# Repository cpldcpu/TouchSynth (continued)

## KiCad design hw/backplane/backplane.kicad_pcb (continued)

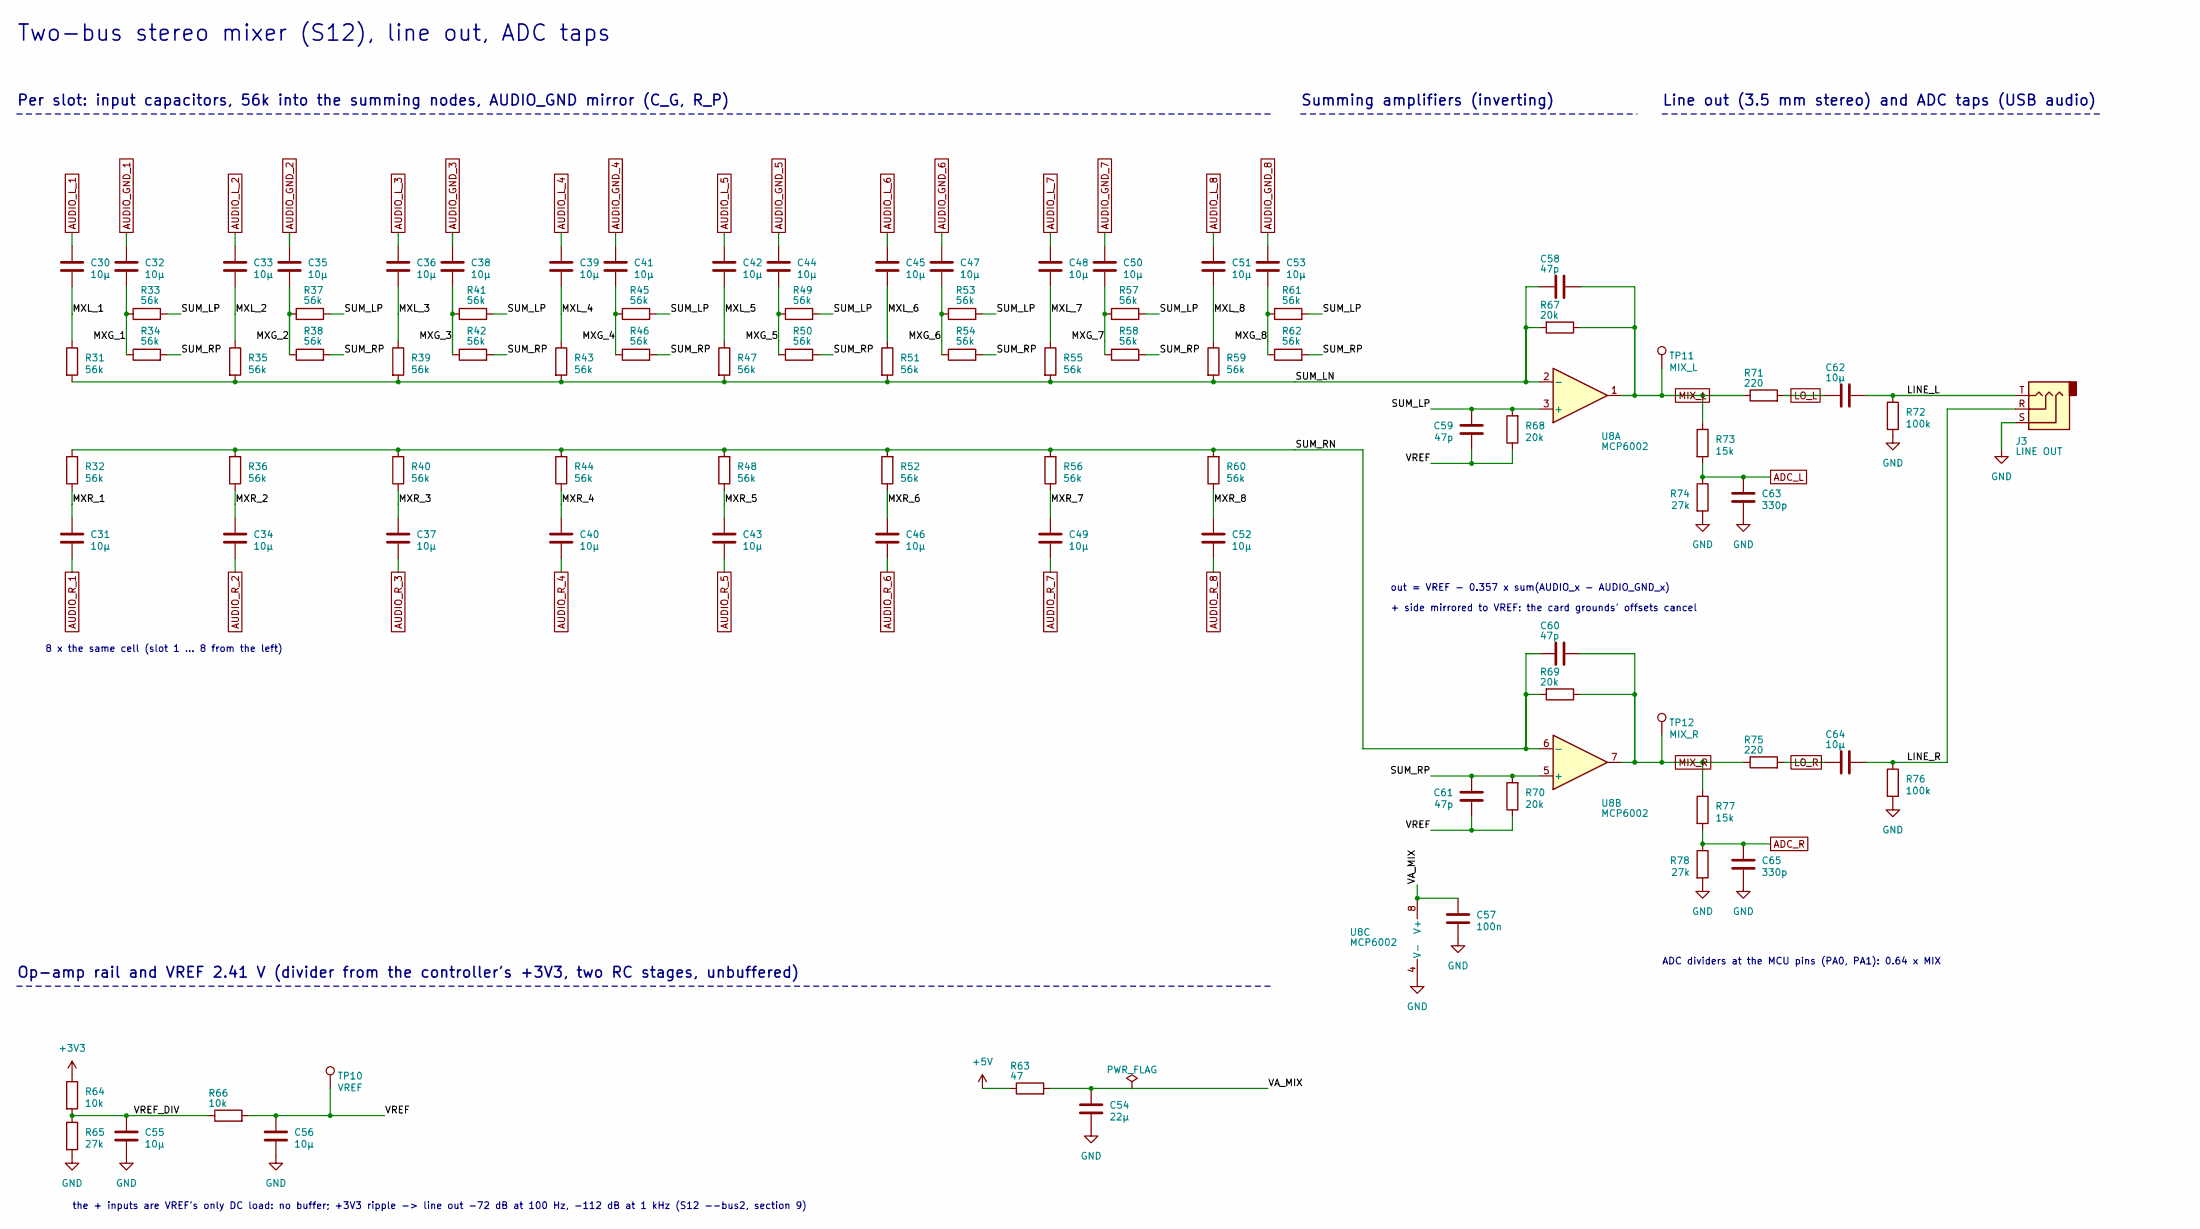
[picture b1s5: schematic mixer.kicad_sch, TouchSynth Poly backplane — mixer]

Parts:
C30, C31, C32, C33, C34, C35, C36, C37, C38, C39, C40, C41, C42, C43, C44, C45, C46, C47, C48, C49, C50, C51, C52, C53: 10µ; C_0805_2012Metric; LCSC C15850
C54: 22µ; C_0805_2012Metric; LCSC C45783
C55, C56, C62, C64: 10µ; C_0603_1608Metric; LCSC C19702
C57: 100n; C_0603_1608Metric; LCSC C14663
C58, C59, C60, C61: 47p; C_0603_1608Metric; LCSC C1671
C63, C65: 330p; C_0603_1608Metric; LCSC C1664
J3: LINE OUT; Jack_3.5mm_CUI_SJ1-3523N_Horizontal
R31, R32, R33, R34, R35, R36, R37, R38, R39, R40, R41, R42, R43, R44, R45, R46, R47, R48, R49, R50, R51, R52, R53, R54, R55, R56, R57, R58, R59, R60, R61, R62: 56k; R_0603_1608Metric; LCSC C23206
R63: 47; R_0603_1608Metric; LCSC C23182
R64, R66: 10k; R_0603_1608Metric; LCSC C25804
R65, R74, R78: 27k; R_0603_1608Metric; LCSC C22967
R67, R68, R69, R70: 20k; R_0603_1608Metric; LCSC C4184
R71, R75: 220; R_0603_1608Metric; LCSC C22962
R72, R76: 100k; R_0603_1608Metric; LCSC C25803
R73, R77: 15k; R_0603_1608Metric; LCSC C22809
TP10: VREF; TestPoint_Pad_D1.0mm
TP11: MIX_L; TestPoint_Pad_D1.0mm
TP12: MIX_R; TestPoint_Pad_D1.0mm
U8: MCP6002; SOIC-8_3.9x4.9mm_P1.27mm; LCSC C7377

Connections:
+3V3: R64.1; also elsewhere on the board
+5V: R63.1; also elsewhere on the board
/mixer/LINE_L: C62.2, J3.T, R72.1
/mixer/LINE_R: C64.2, J3.R, R76.1
/mixer/MXG_1: C32.2, R33.1, R34.1
/mixer/MXG_2: C35.2, R37.1, R38.1
/mixer/MXG_3: C38.2, R41.1, R42.1
/mixer/MXG_4: C41.2, R45.1, R46.1
/mixer/MXG_5: C44.2, R49.1, R50.1
/mixer/MXG_6: C47.2, R53.1, R54.1
/mixer/MXG_7: C50.2, R57.1, R58.1
/mixer/MXG_8: C53.2, R61.1, R62.1
/mixer/MXL_1: C30.2, R31.1
/mixer/MXL_2: C33.2, R35.1
/mixer/MXL_3: C36.2, R39.1
/mixer/MXL_4: C39.2, R43.1
/mixer/MXL_5: C42.2, R47.1
/mixer/MXL_6: C45.2, R51.1
/mixer/MXL_7: C48.2, R55.1
/mixer/MXL_8: C51.2, R59.1
/mixer/MXR_1: C31.2, R32.1
/mixer/MXR_2: C34.2, R36.1
/mixer/MXR_3: C37.2, R40.1
/mixer/MXR_4: C40.2, R44.1
/mixer/MXR_5: C43.2, R48.1
/mixer/MXR_6: C46.2, R52.1
/mixer/MXR_7: C49.2, R56.1
/mixer/MXR_8: C52.2, R60.1
/mixer/SUM_LN: C58.2, R31.2, R35.2, R39.2, R43.2, R47.2, R51.2, R55.2, R59.2, R67.2, U8.2 (-)
/mixer/SUM_LP: C59.2, R33.2, R37.2, R41.2, R45.2, R49.2, R53.2, R57.2, R61.2, R68.2, U8.3 (+)
/mixer/SUM_RN: C60.2, R32.2, R36.2, R40.2, R44.2, R48.2, R52.2, R56.2, R60.2, R69.2, U8.6 (-)
/mixer/SUM_RP: C61.2, R34.2, R38.2, R42.2, R46.2, R50.2, R54.2, R58.2, R62.2, R70.2, U8.5 (+)
/mixer/VA_MIX: C54.1, C57.1, R63.2, U8.8 (V+)
/mixer/VREF: C56.1, C59.1, C61.1, R66.2, R68.1, R70.1, TP10.1
/mixer/VREF_DIV: C55.1, R64.2, R65.1, R66.1
ADC_L: C63.1, R73.2, R74.1; also elsewhere on the board
ADC_R: C65.1, R77.2, R78.1; also elsewhere on the board
AUDIO_GND_1: C32.1; also elsewhere on the board
AUDIO_GND_2: C35.1; also elsewhere on the board
AUDIO_GND_3: C38.1; also elsewhere on the board
AUDIO_GND_4: C41.1; also elsewhere on the board
AUDIO_GND_5: C44.1; also elsewhere on the board
AUDIO_GND_6: C47.1; also elsewhere on the board
AUDIO_GND_7: C50.1; also elsewhere on the board
AUDIO_GND_8: C53.1; also elsewhere on the board
AUDIO_L_1: C30.1; also elsewhere on the board
AUDIO_L_2: C33.1; also elsewhere on the board
AUDIO_L_3: C36.1; also elsewhere on the board
AUDIO_L_4: C39.1; also elsewhere on the board
AUDIO_L_5: C42.1; also elsewhere on the board
AUDIO_L_6: C45.1; also elsewhere on the board
AUDIO_L_7: C48.1; also elsewhere on the board
AUDIO_L_8: C51.1; also elsewhere on the board
AUDIO_R_1: C31.1; also elsewhere on the board
AUDIO_R_2: C34.1; also elsewhere on the board
AUDIO_R_3: C37.1; also elsewhere on the board
AUDIO_R_4: C40.1; also elsewhere on the board
AUDIO_R_5: C43.1; also elsewhere on the board
AUDIO_R_6: C46.1; also elsewhere on the board
AUDIO_R_7: C49.1; also elsewhere on the board
AUDIO_R_8: C52.1; also elsewhere on the board
GND: C54.2, C55.2, C56.2, C57.2, C63.2, C65.2, J3.S, R65.2, R72.2, R74.2, R76.2, R78.2, U8.4 (V-); also elsewhere on the board
LO_L: C62.1, R71.2; also elsewhere on the board
LO_R: C64.1, R75.2; also elsewhere on the board
MIX_L: C58.1, R67.1, R71.1, R73.1, TP11.1, U8.1; also elsewhere on the board
MIX_R: C60.1, R69.1, R75.1, R77.1, TP12.1, U8.7; also elsewhere on the board

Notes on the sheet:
Two-bus stereo mixer (S12), line out, ADC taps
Per slot: input capacitors, 56k into the summing nodes, AUDIO_GND mirror (C_G, R_P)
8 x the same cell (slot 1 ... 8 from the left)
Summing amplifiers (inverting)
out = VREF - 0.357 x sum(AUDIO_x - AUDIO_GND_x)
+ side mirrored to VREF: the card grounds' offsets cancel
Line out (3.5 mm stereo) and ADC taps (USB audio)
ADC dividers at the MCU pins (PA0, PA1): 0.64 x MIX
Op-amp rail and VREF 2.41 V (divider from the controller's +3V3, two RC stages, unbuffered)
the + inputs are VREF's only DC load: no buffer; +3V3 ripple -> line out -72 dB at 100 Hz, -112 dB at 1 kHz (S12 --bus2, section 9)

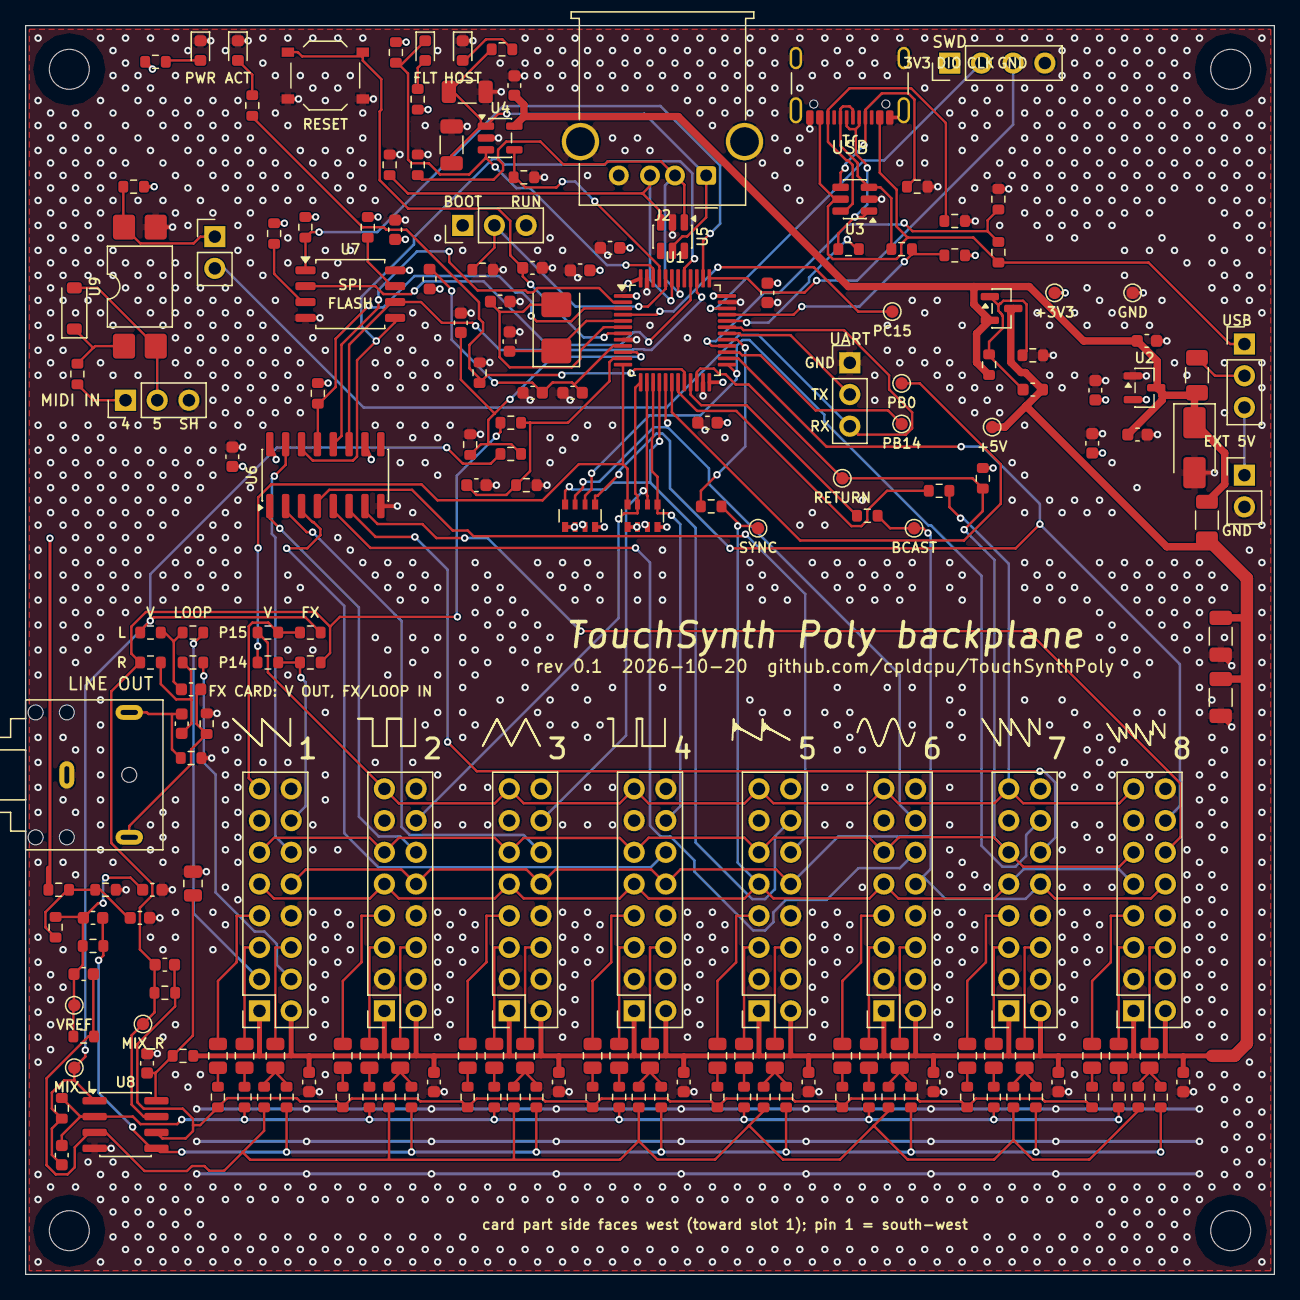
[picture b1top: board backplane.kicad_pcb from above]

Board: 4 copper layers, 100.0 x 100.0 mm, 205 parts (0 on the bottom side), 139 nets.

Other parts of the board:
H1, H2, H3, H4: M3; MountingHole_3.2mm_M3

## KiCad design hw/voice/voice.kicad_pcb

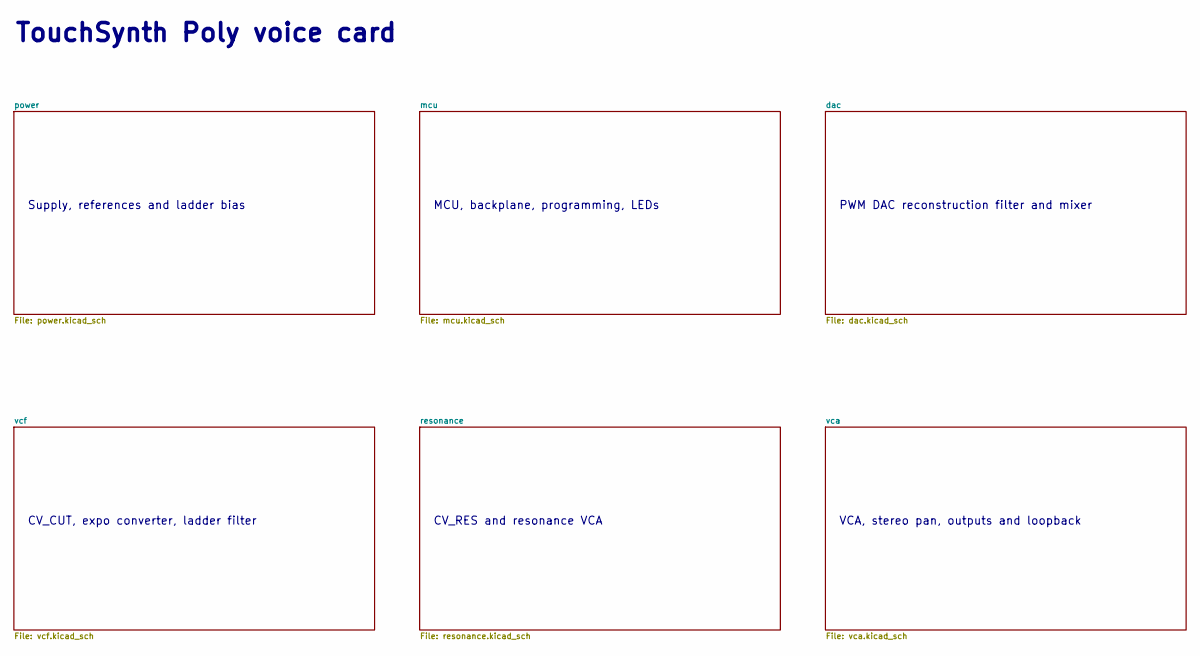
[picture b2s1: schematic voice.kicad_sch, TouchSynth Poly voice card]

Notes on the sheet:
Supply, references and ladder bias
MCU, backplane, programming, LEDs
PWM DAC reconstruction filter and mixer
CV_CUT, expo converter, ladder filter
CV_RES and resonance VCA
VCA, stereo pan, outputs and loopback
TouchSynth Poly voice card

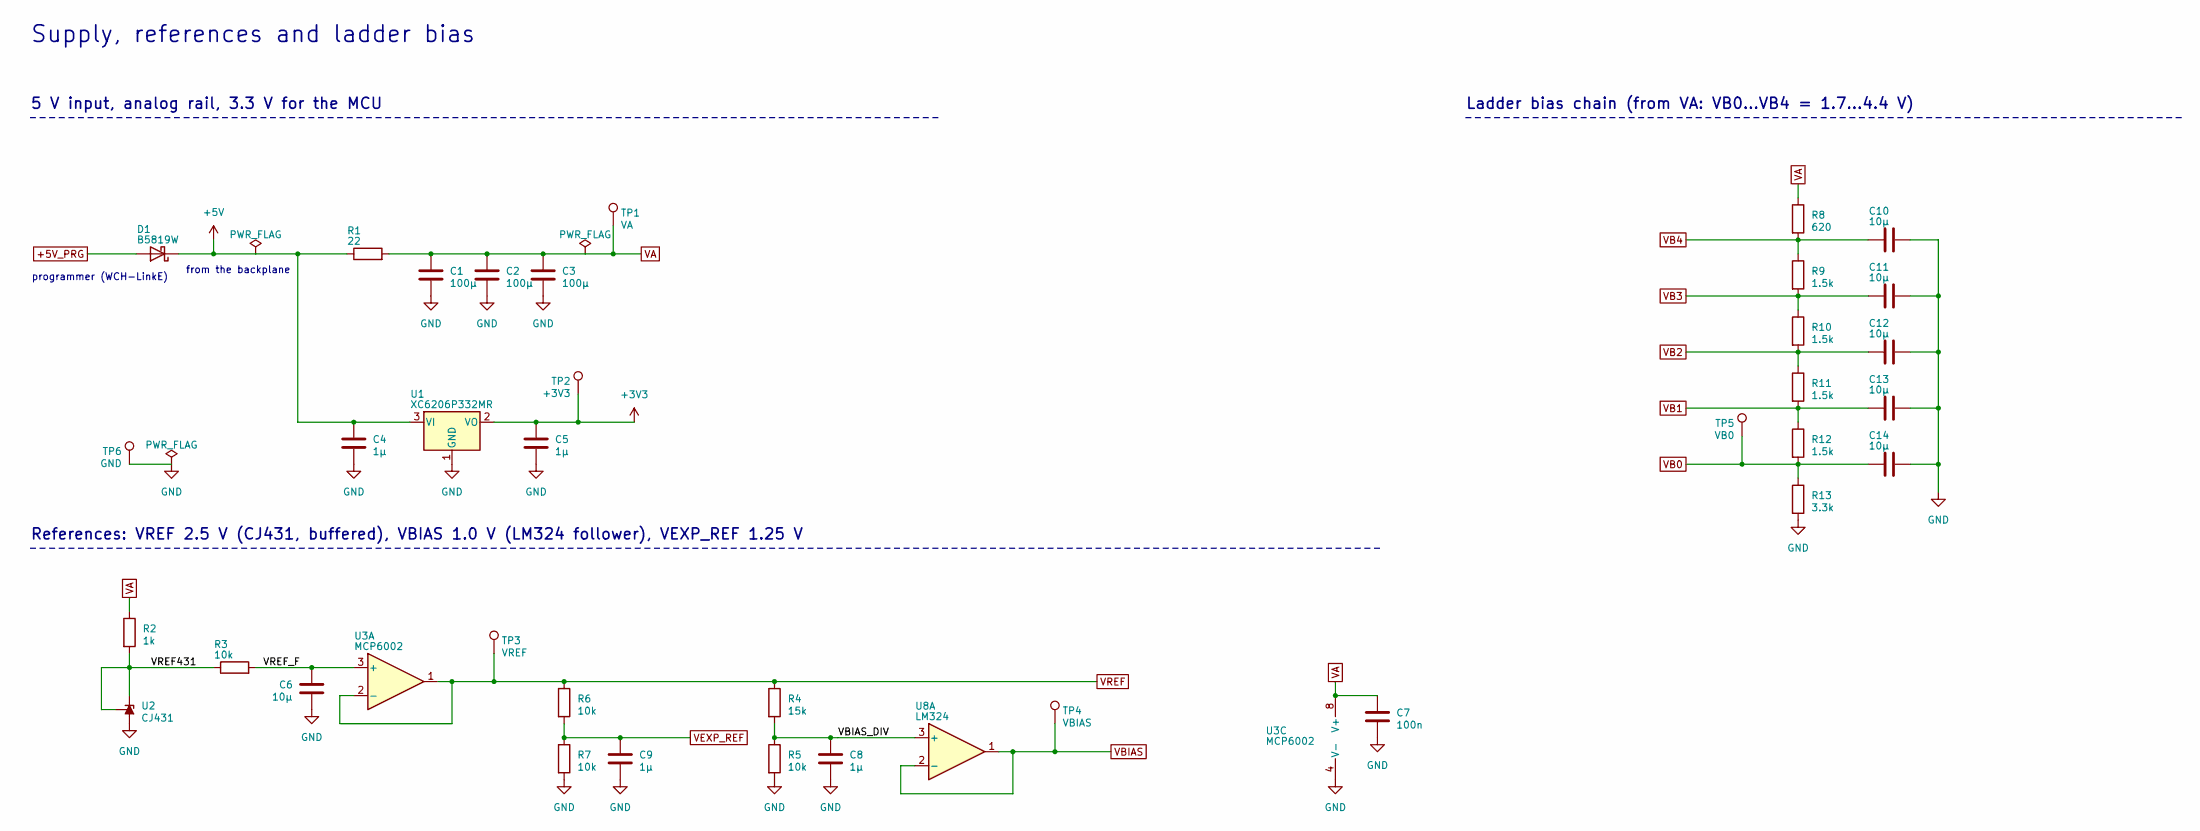
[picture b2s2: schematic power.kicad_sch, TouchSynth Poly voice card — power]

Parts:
C1, C2, C3: 100µ; C_1206_3216Metric; LCSC C15008
C4, C5, C8, C9: 1µ; C_0402_1005Metric; LCSC C52923
C6, C12, C13, C14: 10µ; C_0402_1005Metric; LCSC C15525
C7: 100n; C_0402_1005Metric; LCSC C1525
C10, C11: 10µ; C_0603_1608Metric; LCSC C19702
D1: B5819W; D_SOD-123; LCSC C8598
R1: 22; R_0402_1005Metric; LCSC C25092
R2: 1k; R_0402_1005Metric; LCSC C11702
R3, R5, R6, R7: 10k; R_0402_1005Metric; LCSC C25744
R4: 15k; R_0402_1005Metric; LCSC C25756
R8: 620; R_0603_1608Metric; LCSC C23220
R9, R10, R11, R12: 1.5k; R_0402_1005Metric; LCSC C25867
R13: 3.3k; R_0402_1005Metric; LCSC C25890
TP1: VA; TestPoint_Pad_D1.0mm
TP2: +3V3; TestPoint_Pad_D1.0mm
TP3: VREF; TestPoint_Pad_D1.0mm
TP4: VBIAS; TestPoint_Pad_D1.0mm
TP5: VB0; TestPoint_Pad_D1.0mm
TP6: GND; TestPoint_Pad_D1.0mm
U1: XC6206P332MR; SOT-23; LCSC C5446
U2: CJ431; SOT-23; LCSC C3113
U3: MCP6002; SOIC-8_3.9x4.9mm_P1.27mm; LCSC C7377
U8: LM324; SOIC-14_3.9x8.7mm_P1.27mm; LCSC C71035

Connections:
+3V3: C5.1, TP2.1, U1.2 (VO); also elsewhere on the board
+5V: C4.1, D1.1 (K), R1.1, U1.3 (VI); also elsewhere on the board
+5V_PRG: D1.2 (A); also elsewhere on the board
/power/VBIAS_DIV: C8.1, R4.2, R5.1, U8.3 (+)
/power/VREF431: R2.2, R3.1, U2.1 (REF), U2.2 (K)
/power/VREF_F: C6.1, R3.2, U3.3 (+)
GND: C1.2, C2.2, C3.2, C4.2, C5.2, C6.2, C7.2, C8.2, C9.2, C10.2, C11.2, C12.2, C13.2, C14.2, R5.2, R7.2, R13.2, TP6.1, U1.1 (GND), U2.3 (A), U3.4 (V-); also elsewhere on the board
VA: C1.1, C2.1, C3.1, C7.1, R1.2, R2.1, R8.1, TP1.1, U3.8 (V+); also elsewhere on the board
VB0: C14.1, R12.2, R13.1, TP5.1; also elsewhere on the board
VB1: C13.1, R11.2, R12.1; also elsewhere on the board
VB2: C12.1, R10.2, R11.1; also elsewhere on the board
VB3: C11.1, R9.2, R10.1; also elsewhere on the board
VB4: C10.1, R8.2, R9.1; also elsewhere on the board
VBIAS: TP4.1, U8.1, U8.2 (-); also elsewhere on the board
VEXP_REF: C9.1, R6.2, R7.1; also elsewhere on the board
VREF: R4.1, R6.1, TP3.1, U3.1, U3.2 (-); also elsewhere on the board

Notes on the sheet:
Supply, references and ladder bias
5 V input, analog rail, 3.3 V for the MCU
programmer (WCH-LinkE)
from the backplane
References: VREF 2.5 V (CJ431, buffered), VBIAS 1.0 V (LM324 follower), VEXP_REF 1.25 V
Ladder bias chain (from VA: VB0...VB4 = 1.7...4.4 V)

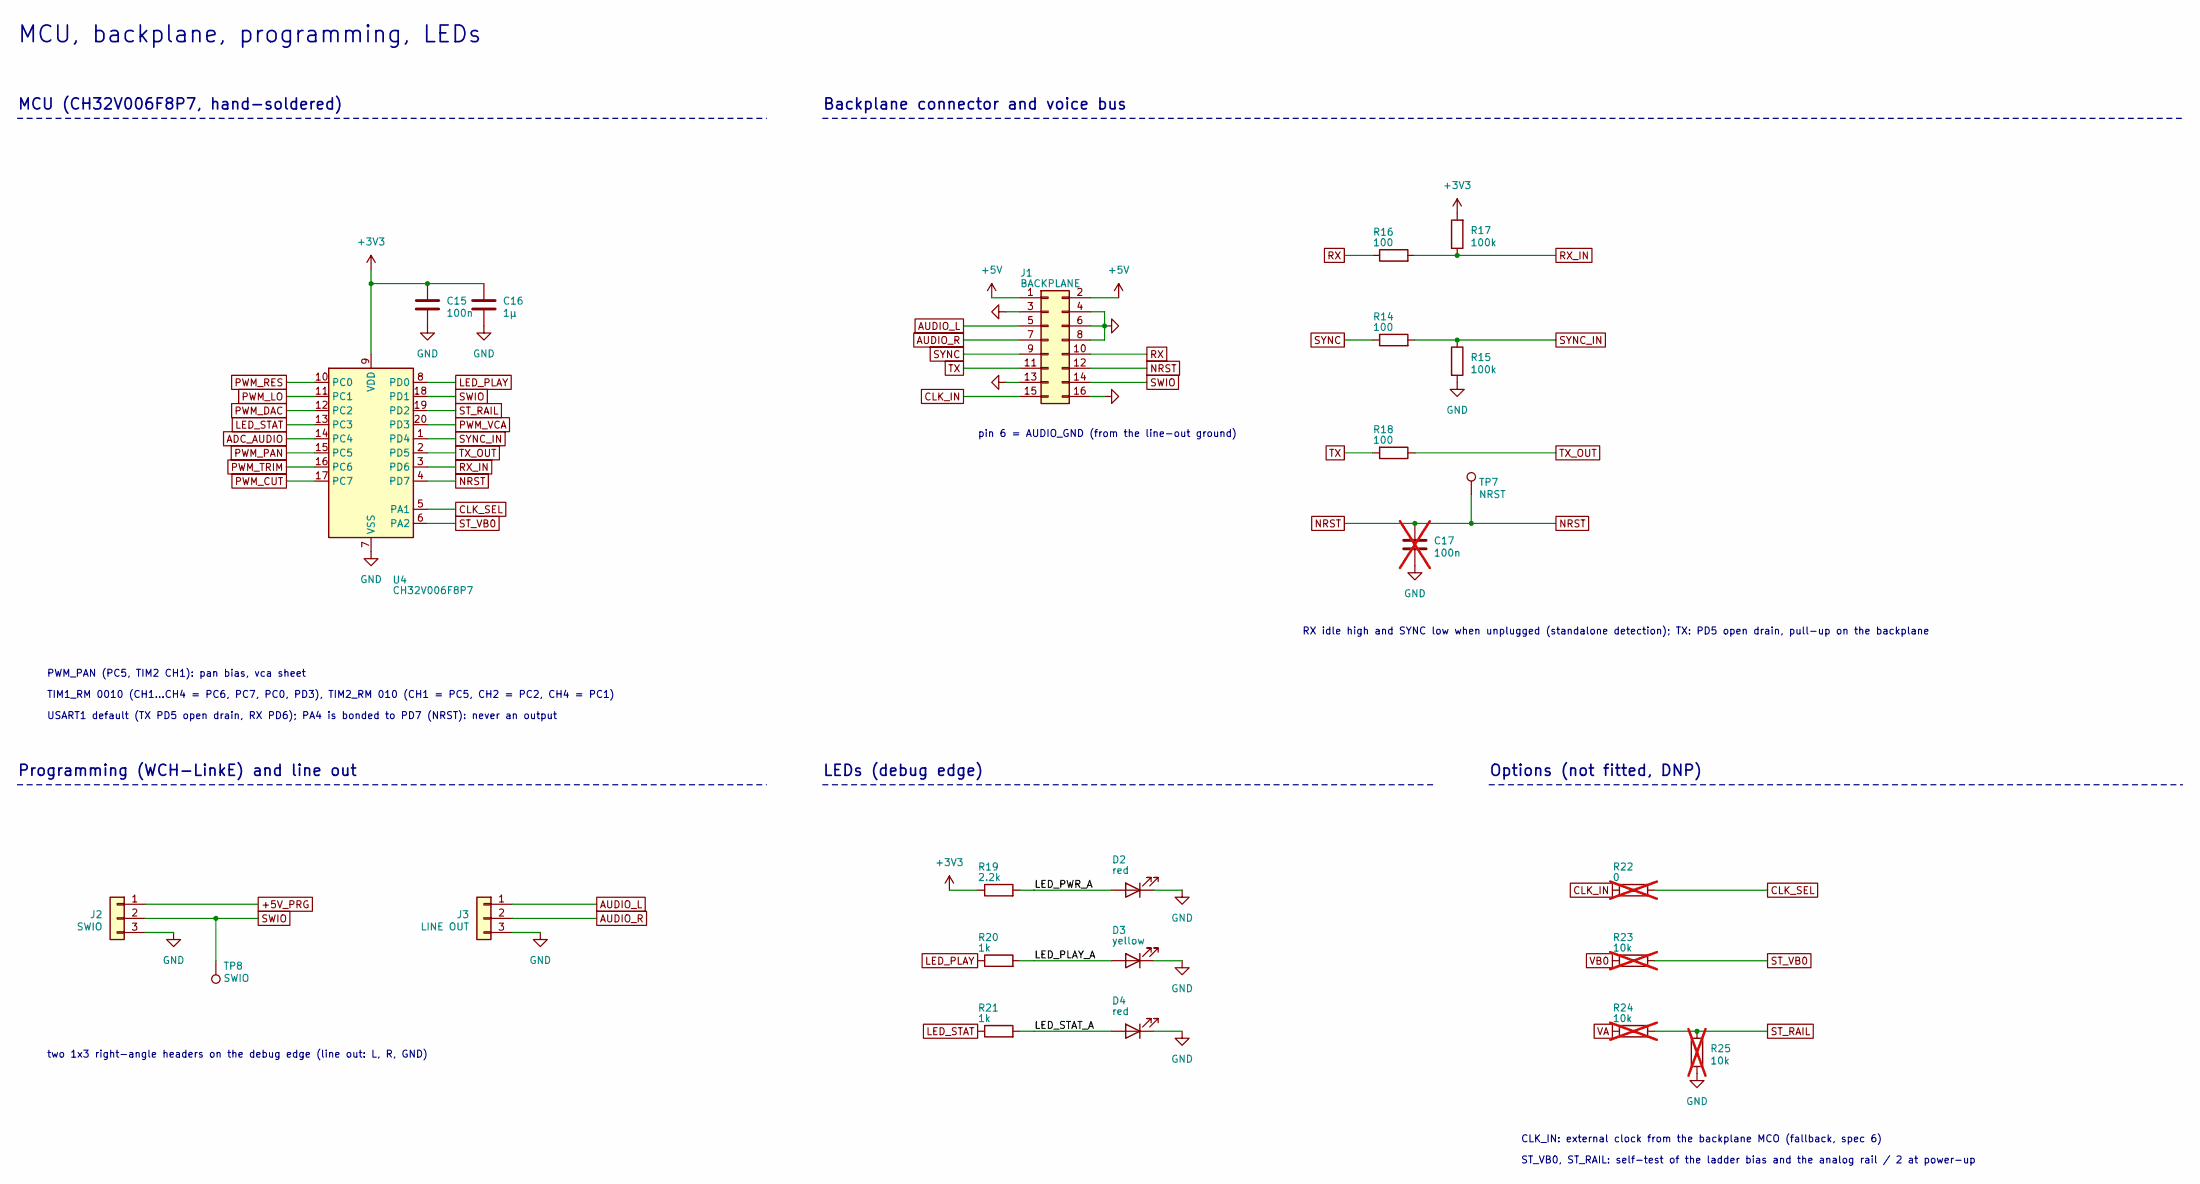
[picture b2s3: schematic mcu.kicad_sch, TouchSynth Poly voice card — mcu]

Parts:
C15: 100n; C_0402_1005Metric; LCSC C1525
C16: 1µ; C_0402_1005Metric; LCSC C52923
C17: 100n; C_0402_1005Metric; LCSC C1525; not fitted
D2, D4: red; LED_0603_1608Metric; LCSC C2286
D3: yellow; LED_0603_1608Metric; LCSC C89811
J1: BACKPLANE; PinHeader_2x08_P2.54mm_Horizontal
J2: SWIO; PinHeader_1x03_P2.54mm_Horizontal
J3: LINE OUT; PinHeader_1x03_P2.54mm_Horizontal
R14, R16, R18: 100; R_0402_1005Metric; LCSC C25076
R15, R17: 100k; R_0402_1005Metric; LCSC C25741
R19: 2.2k; R_0402_1005Metric; LCSC C25879
R20, R21: 1k; R_0402_1005Metric; LCSC C11702
R22: 0; R_0402_1005Metric; LCSC C17168; not fitted
R23, R24, R25: 10k; R_0402_1005Metric; LCSC C25744; not fitted
TP7: NRST; TestPoint_Pad_D1.0mm
TP8: SWIO; TestPoint_Pad_D1.0mm
U4: CH32V006F8P7; TSSOP-20_4.4x6.5mm_P0.65mm

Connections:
+3V3: C15.1, C16.1, R17.2, R19.1, U4.9 (VDD); also elsewhere on the board
+5V: J1.1, J1.2; also elsewhere on the board
+5V_PRG: J2.1; also elsewhere on the board
/mcu/LED_PLAY_A: D3.2 (A), R20.2
/mcu/LED_PWR_A: D2.2 (A), R19.2
/mcu/LED_STAT_A: D4.2 (A), R21.2
ADC_AUDIO: U4.14 (PC4); also elsewhere on the board
AUDIO_L: J1.5, J3.1; also elsewhere on the board
AUDIO_R: J1.7, J3.2; also elsewhere on the board
CLK_IN: J1.15, R22.1
CLK_SEL: R22.2, U4.5 (PA1)
GND: C15.2, C16.2, C17.2, D2.1 (K), D3.1 (K), D4.1 (K), J1.3, J1.4, J1.6, J1.8, J1.13, J1.16, J2.3, J3.3, R15.2, R25.2, U4.7 (VSS); also elsewhere on the board
LED_PLAY: R20.1, U4.8 (PD0)
LED_STAT: R21.1, U4.13 (PC3)
NRST: C17.1, J1.12, TP7.1, U4.4 (PD7)
PWM_CUT: U4.17 (PC7); also elsewhere on the board
PWM_DAC: U4.12 (PC2); also elsewhere on the board
PWM_LO: U4.11 (PC1); also elsewhere on the board
PWM_PAN: U4.15 (PC5); also elsewhere on the board
PWM_RES: U4.10 (PC0); also elsewhere on the board
PWM_TRIM: U4.16 (PC6); also elsewhere on the board
PWM_VCA: U4.20 (PD3); also elsewhere on the board
RX: J1.10, R16.1
RX_IN: R16.2, R17.1, U4.3 (PD6)
ST_RAIL: R24.2, R25.1, U4.19 (PD2)
ST_VB0: R23.2, U4.6 (PA2)
SWIO: J1.14, J2.2, TP8.1, U4.18 (PD1)
SYNC: J1.9, R14.1
SYNC_IN: R14.2, R15.1, U4.1 (PD4)
TX: J1.11, R18.2
TX_OUT: R18.1, U4.2 (PD5)
VA: R24.1; also elsewhere on the board
VB0: R23.1; also elsewhere on the board

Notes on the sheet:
MCU, backplane, programming, LEDs
MCU (CH32V006F8P7, hand-soldered)
PWM_PAN (PC5, TIM2 CH1): pan bias, vca sheet
TIM1_RM 0010 (CH1...CH4 = PC6, PC7, PC0, PD3), TIM2_RM 010 (CH1 = PC5, CH2 = PC2, CH4 = PC1)
USART1 default (TX PD5 open drain, RX PD6); PA4 is bonded to PD7 (NRST): never an output
Backplane connector and voice bus
pin 6 = AUDIO_GND (from the line-out ground)
RX idle high and SYNC low when unplugged (standalone detection); TX: PD5 open drain, pull-up on the backplane
Programming (WCH-LinkE) and line out
two 1x3 right-angle headers on the debug edge (line out: L, R, GND)
LEDs (debug edge)
Options (not fitted, DNP)
CLK_IN: external clock from the backplane MCO (fallback, spec 6)
ST_VB0, ST_RAIL: self-test of the ladder bias and the analog rail / 2 at power-up

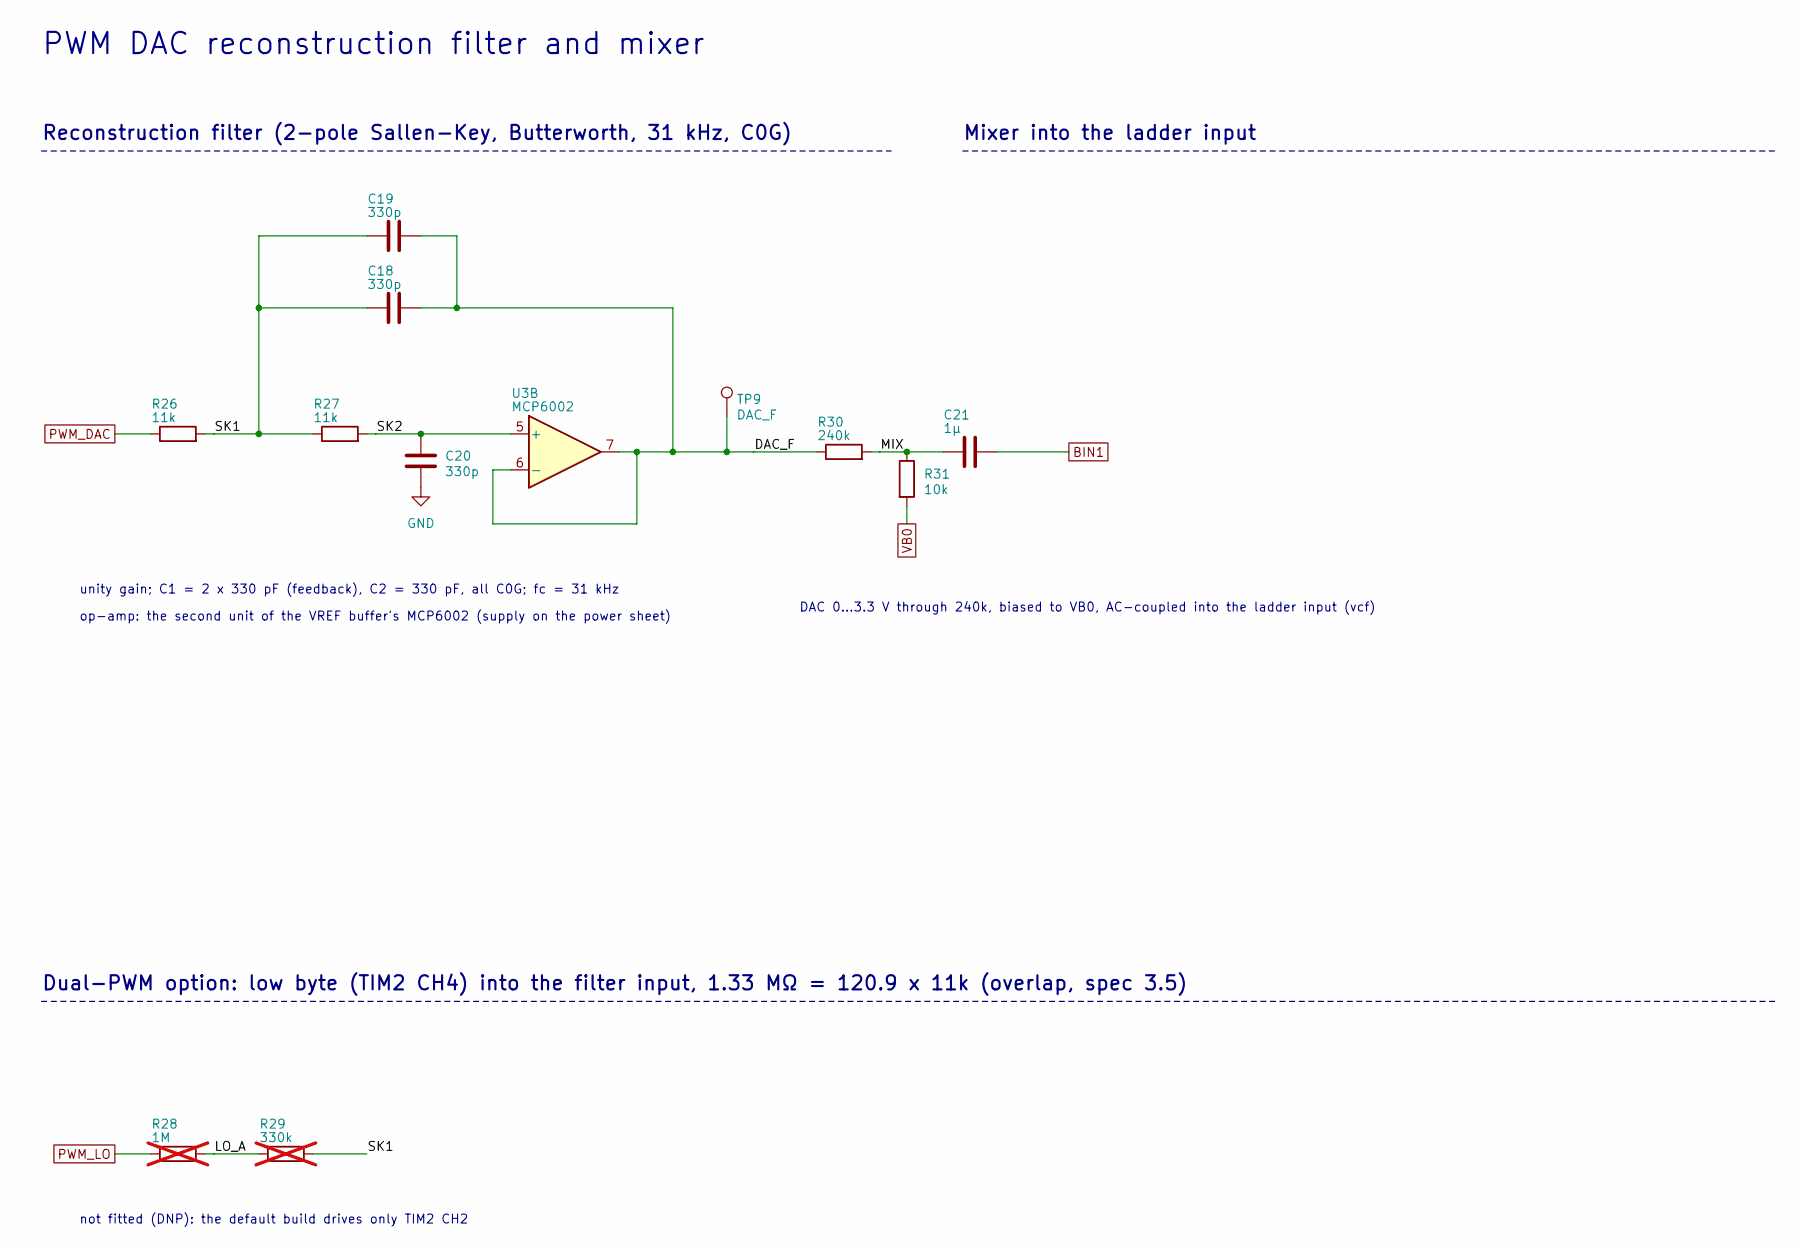
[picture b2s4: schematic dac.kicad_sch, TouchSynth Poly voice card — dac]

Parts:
C18, C19, C20: 330p; C_0402_1005Metric; LCSC C13533
C21: 1µ; C_0402_1005Metric; LCSC C52923
R26, R27: 11k; R_0603_1608Metric; LCSC C25950
R28: 1M; R_0402_1005Metric; LCSC C26083; not fitted
R29: 330k; R_0402_1005Metric; LCSC C25778; not fitted
R30: 240k; R_0603_1608Metric; LCSC C4197
R31: 10k; R_0402_1005Metric; LCSC C25744
TP9: DAC_F; TestPoint_Pad_D1.0mm
U3: MCP6002; SOIC-8_3.9x4.9mm_P1.27mm; LCSC C7377

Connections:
/dac/DAC_F: C18.2, C19.2, R30.1, TP9.1, U3.6 (-), U3.7
/dac/LO_A: R28.2, R29.1
/dac/MIX: C21.1, R30.2, R31.1
/dac/SK1: C18.1, C19.1, R26.2, R27.1, R29.2
/dac/SK2: C20.1, R27.2, U3.5 (+)
BIN1: C21.2; also elsewhere on the board
GND: C20.2; also elsewhere on the board
PWM_DAC: R26.1; also elsewhere on the board
PWM_LO: R28.1; also elsewhere on the board
VB0: R31.2; also elsewhere on the board

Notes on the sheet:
PWM DAC reconstruction filter and mixer
Reconstruction filter (2-pole Sallen-Key, Butterworth, 31 kHz, C0G)
unity gain; C1 = 2 x 330 pF (feedback), C2 = 330 pF, all C0G; fc = 31 kHz
op-amp: the second unit of the VREF buffer's MCP6002 (supply on the power sheet)
Mixer into the ladder input
DAC 0...3.3 V through 240k, biased to VB0, AC-coupled into the ladder input (vcf)
Dual-PWM option: low byte (TIM2 CH4) into the filter input, 1.33 MΩ = 120.9 x 11k (overlap, spec 3.5)
not fitted (DNP): the default build drives only TIM2 CH2

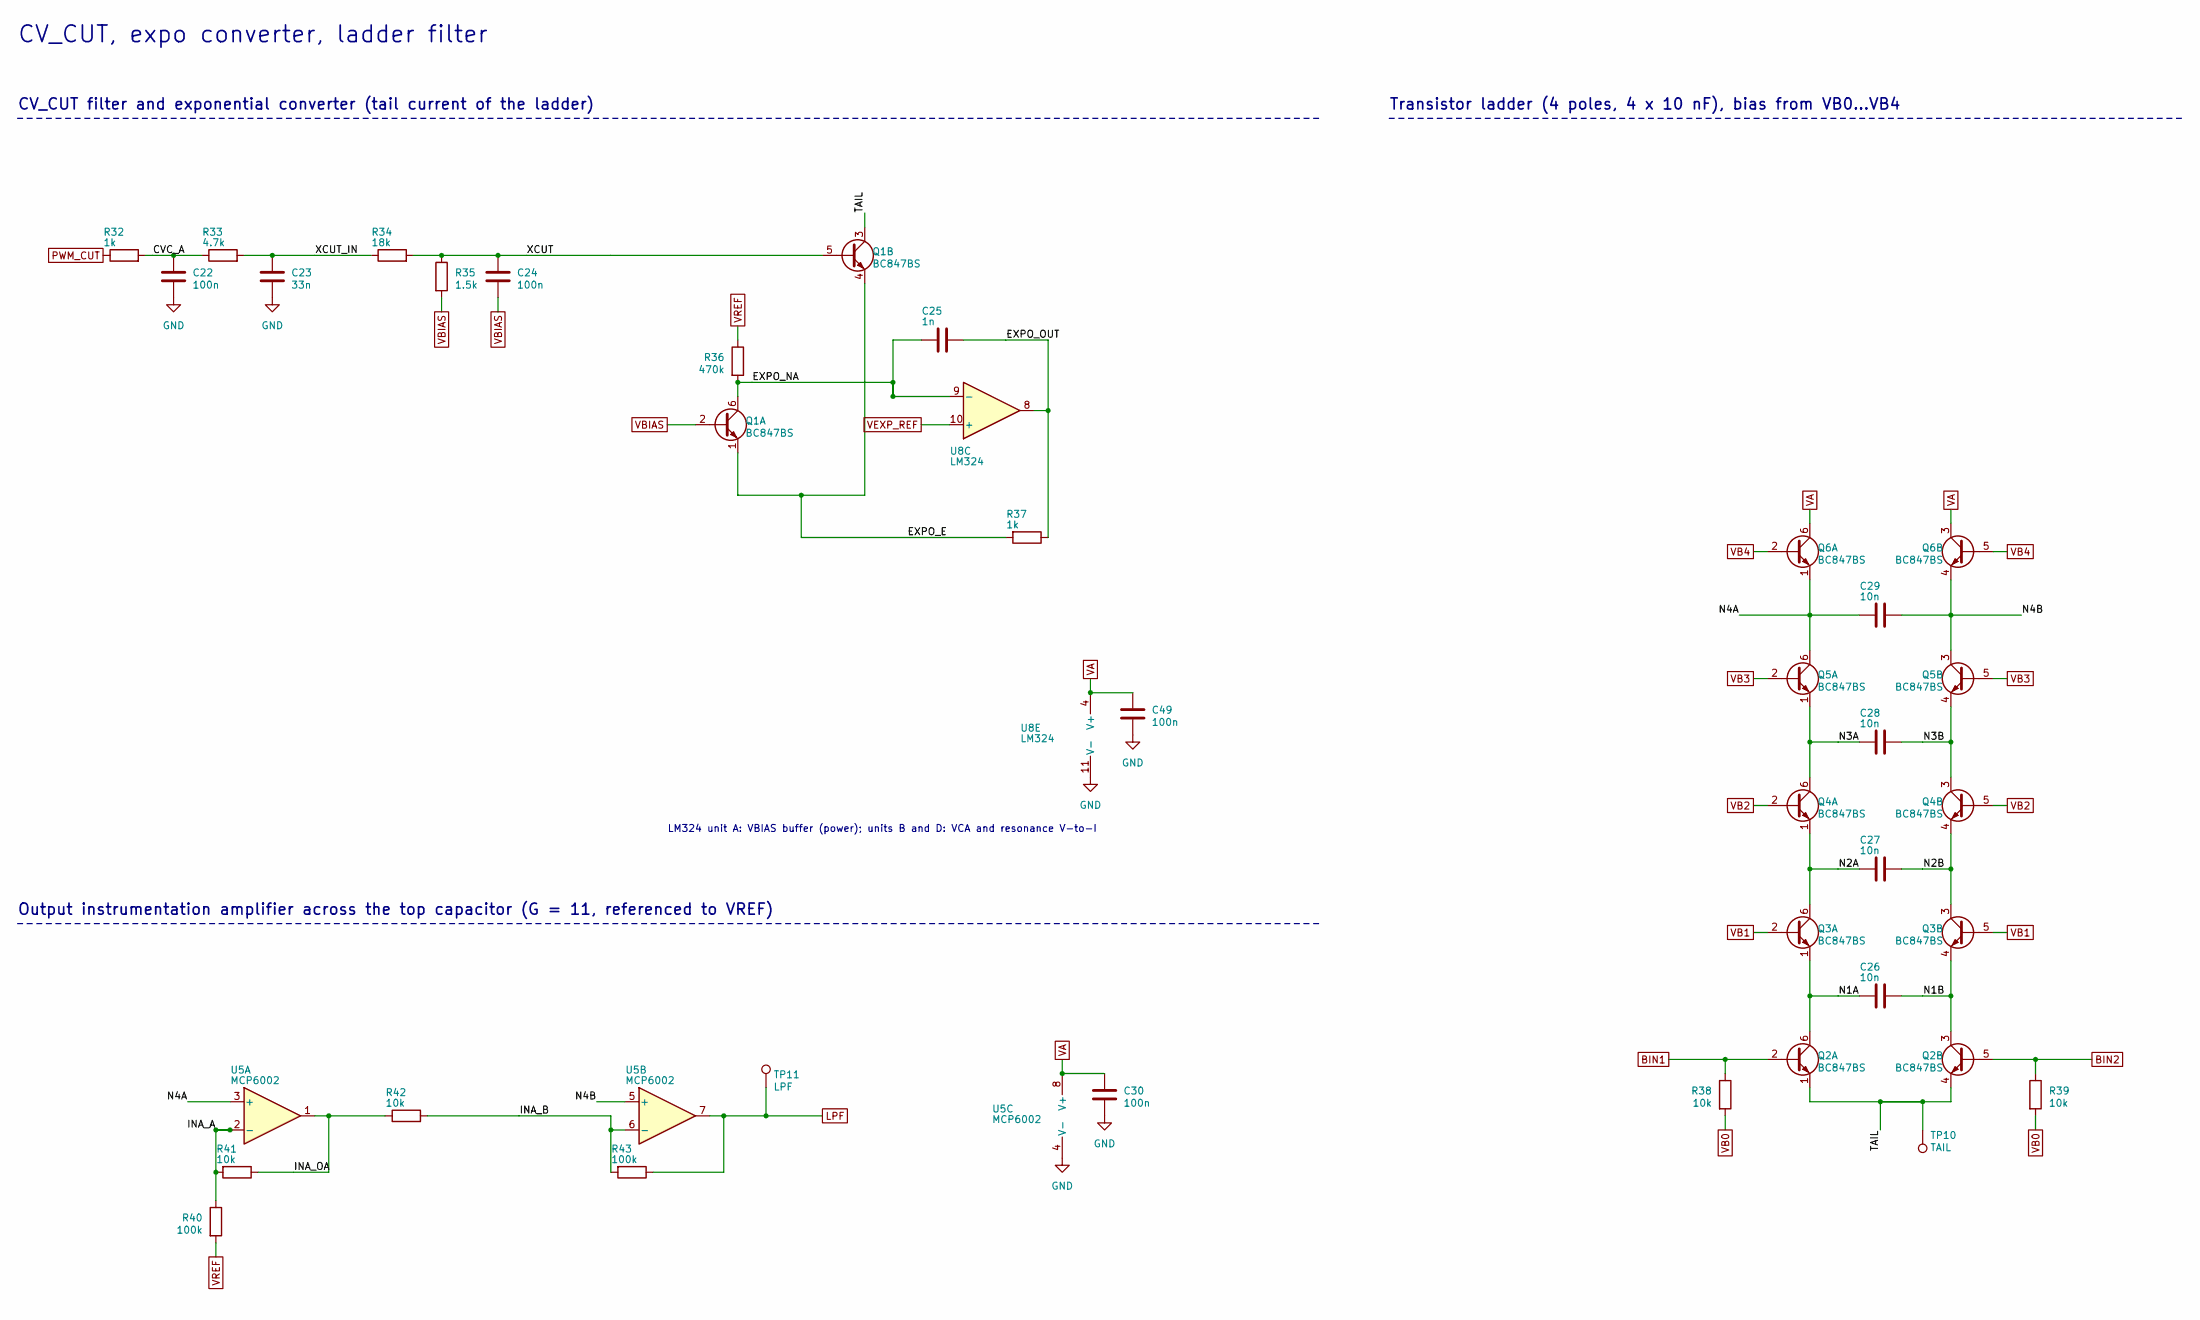
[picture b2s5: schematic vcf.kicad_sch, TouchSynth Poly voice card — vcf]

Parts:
C22, C24, C30, C49: 100n; C_0402_1005Metric; LCSC C1525
C23: 33n; C_0603_1608Metric; LCSC C21117
C25: 1n; C_0402_1005Metric; LCSC C1523
C26, C27, C28, C29: 10n; C_0402_1005Metric; LCSC C15195
Q1, Q2, Q3, Q4, Q5, Q6: BC847BS; SOT-363_SC-70-6; LCSC C41375126
R32, R37: 1k; R_0402_1005Metric; LCSC C11702
R33: 4.7k; R_0402_1005Metric; LCSC C25900
R34: 18k; R_0402_1005Metric; LCSC C25762
R35: 1.5k; R_0402_1005Metric; LCSC C25867
R36: 470k; R_0402_1005Metric; LCSC C25790
R38, R39, R41, R42: 10k; R_0402_1005Metric; LCSC C25744
R40, R43: 100k; R_0402_1005Metric; LCSC C25741
TP10: TAIL; TestPoint_Pad_D1.0mm
TP11: LPF; TestPoint_Pad_D1.0mm
U5: MCP6002; SOIC-8_3.9x4.9mm_P1.27mm; LCSC C7377
U8: LM324; SOIC-14_3.9x8.7mm_P1.27mm; LCSC C71035

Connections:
/vcf/CVC_A: C22.1, R32.2, R33.1
/vcf/EXPO_E: Q1.1 (E1), Q1.4 (E2), R37.2
/vcf/EXPO_NA: C25.2, Q1.6 (C1), R36.2, U8.9 (-)
/vcf/EXPO_OUT: C25.1, R37.1, U8.8
/vcf/INA_A: R40.1, R41.2, U5.2 (-)
/vcf/INA_B: R42.2, R43.2, U5.6 (-)
/vcf/INA_OA: R41.1, R42.1, U5.1
/vcf/N1A: C26.1, Q2.6 (C1), Q3.1 (E1)
/vcf/N1B: C26.2, Q2.3 (C2), Q3.4 (E2)
/vcf/N2A: C27.1, Q3.6 (C1), Q4.1 (E1)
/vcf/N2B: C27.2, Q3.3 (C2), Q4.4 (E2)
/vcf/N3A: C28.1, Q4.6 (C1), Q5.1 (E1)
/vcf/N3B: C28.2, Q4.3 (C2), Q5.4 (E2)
/vcf/N4A: C29.1, Q5.6 (C1), Q6.1 (E1), U5.3 (+)
/vcf/N4B: C29.2, Q5.3 (C2), Q6.4 (E2), U5.5 (+)
/vcf/TAIL: Q1.3 (C2), Q2.1 (E1), Q2.4 (E2), TP10.1
/vcf/XCUT: C24.1, Q1.5 (B2), R34.2, R35.1
/vcf/XCUT_IN: C23.1, R33.2, R34.1
BIN1: Q2.2 (B1), R38.1; also elsewhere on the board
BIN2: Q2.5 (B2), R39.1; also elsewhere on the board
GND: C22.2, C23.2, C30.2, C49.2, U5.4 (V-), U8.11 (V-); also elsewhere on the board
LPF: R43.1, TP11.1, U5.7; also elsewhere on the board
PWM_CUT: R32.1; also elsewhere on the board
VA: C30.1, C49.1, Q6.3 (C2), Q6.6 (C1), U5.8 (V+), U8.4 (V+); also elsewhere on the board
VB0: R38.2, R39.2; also elsewhere on the board
VB1: Q3.2 (B1), Q3.5 (B2); also elsewhere on the board
VB2: Q4.2 (B1), Q4.5 (B2); also elsewhere on the board
VB3: Q5.2 (B1), Q5.5 (B2); also elsewhere on the board
VB4: Q6.2 (B1), Q6.5 (B2); also elsewhere on the board
VBIAS: C24.2, Q1.2 (B1), R35.2; also elsewhere on the board
VEXP_REF: U8.10 (+); also elsewhere on the board
VREF: R36.1, R40.2; also elsewhere on the board

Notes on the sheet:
CV_CUT, expo converter, ladder filter
CV_CUT filter and exponential converter (tail current of the ladder)
LM324 unit A: VBIAS buffer (power); units B and D: VCA and resonance V-to-I
Transistor ladder (4 poles, 4 x 10 nF), bias from VB0...VB4
Output instrumentation amplifier across the top capacitor (G = 11, referenced to VREF)
